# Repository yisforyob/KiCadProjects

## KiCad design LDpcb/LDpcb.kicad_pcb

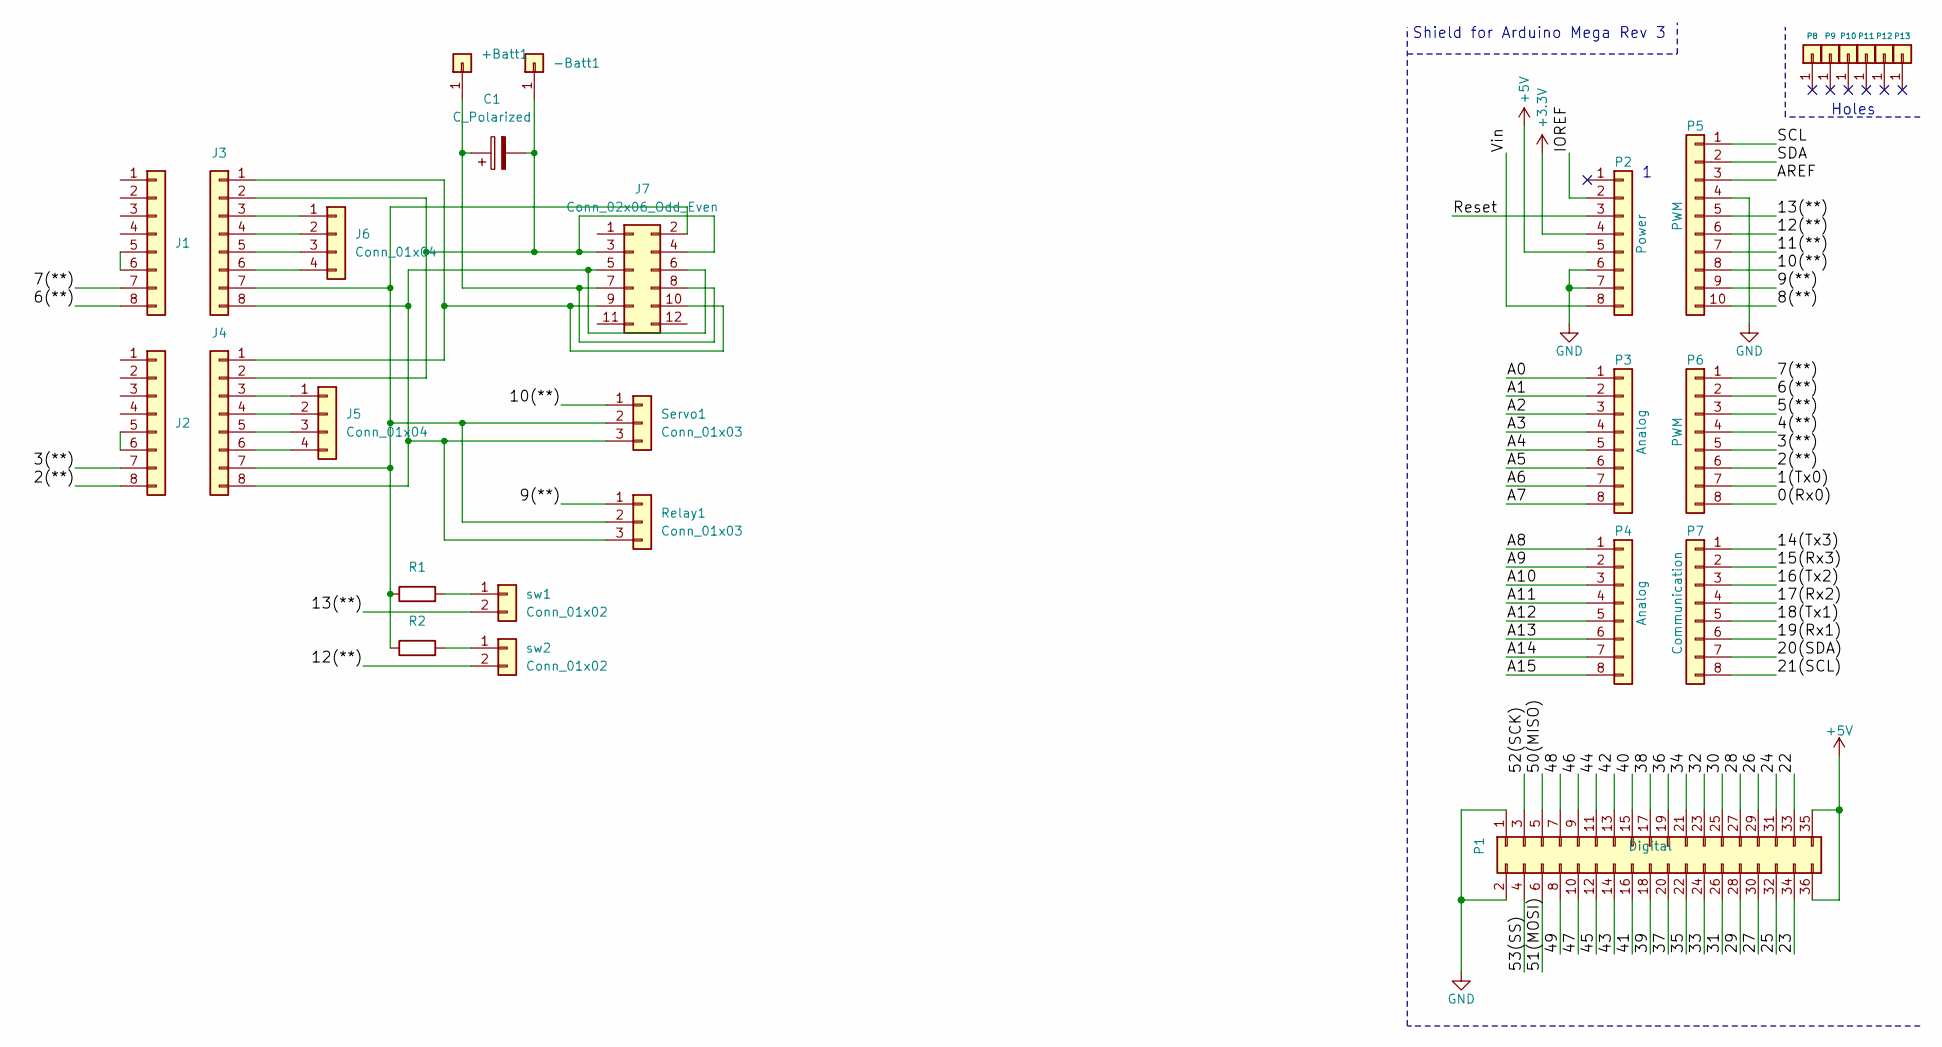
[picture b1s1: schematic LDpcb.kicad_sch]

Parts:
+Batt1: Conn_01x01; TestPoint_THTPad_D4.0mm_Drill2.0mm
-Batt1: Conn_01x01; TestPoint_THTPad_D4.0mm_Drill2.0mm
C1: C_Polarized; CP_Elec_8x6.2
J1, J2, J3, J4: Conn_01x08; PinSocket_1x08_P2.54mm_Vertical
J5, J6: Conn_01x04; PinHeader_1x04_P2.54mm_Vertical
J7: Conn_02x06_Odd_Even; PinSocket_2x06_P2.54mm_Vertical
P1: Digital; Socket_Strip_Arduino_2x18
P2: Power; Socket_Strip_Arduino_1x08
P3, P4: Analog; Socket_Strip_Arduino_1x08
P5: PWM; Socket_Strip_Arduino_1x10
P6: PWM; Socket_Strip_Arduino_1x08
P7: Communication; Socket_Strip_Arduino_1x08
P8, P9, P10, P11, P12, P13: CONN_01X01; Arduino_1pin
R1, R2: R; R_0805_2012Metric_Pad1.20x1.40mm_HandSolder
Relay1: Conn_01x03; PinSocket_1x03_P2.54mm_Vertical
Servo1: Conn_01x03; PinHeader_1x03_P2.54mm_Vertical
sw1, sw2: Conn_01x02; PinSocket_1x02_P2.54mm_Vertical

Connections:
+3V3: P2.4
+5V: P1.35, P1.36, P2.5
/0(Rx0): P6.8
/1(Tx0): P6.7
/2(**): J2.8, P6.6
/3(**): J2.7, P6.5
/4(**): P6.4
/5(**): P6.3
/6(**): J1.8, P6.2
/7(**): J1.7, P6.1
/8(**): P5.10
/9(**): P5.9, Relay1.1
/10(**): P5.8, Servo1.1
/11(**): P5.7
/12(**): P5.6, sw2.2
/13(**): P5.5, sw1.2
/14(Tx3): P7.1
/15(Rx3): P7.2
/16(Tx2): P7.3
/17(Rx2): P7.4
/18(Tx1): P7.5
/19(Rx1): P7.6
/20(SDA): P7.7
/21(SCL): P7.8
/22: P1.33
/23: P1.34
/24: P1.31
/25: P1.32
/26: P1.29
/27: P1.30
/28: P1.27
/29: P1.28
/30: P1.25
/31: P1.26
/32: P1.23
/33: P1.24
/34: P1.21
/35: P1.22
/36: P1.19
/37: P1.20
/38: P1.17
/39: P1.18
/40: P1.15
/41: P1.16
/42: P1.13
/43: P1.14
/44: P1.11
/45: P1.12
/46: P1.9
/47: P1.10
/48: P1.7
/49: P1.8
/50(MISO): P1.5
/51(MOSI): P1.6
/52(SCK): P1.3
/53(SS): P1.4
/A0: P3.1
/A1: P3.2
/A2: P3.3
/A3: P3.4
/A4: P3.5
/A5: P3.6
/A6: P3.7
/A7: P3.8
/A8: P4.1
/A9: P4.2
/A10: P4.3
/A11: P4.4
/A12: P4.5
/A13: P4.6
/A14: P4.7
/A15: P4.8
/AREF: P5.3
/IOREF: P2.2
/Reset: P2.3
/SCL: P5.1
/SDA: P5.2
/Vin: P2.8
GND: P1.1, P1.2, P2.6, P2.7, P5.4
unnamed: +Batt1.1, C1.1, J7.7, J7.8
unnamed: -Batt1.1, C1.2, J3.2, J4.2, J7.3, J7.4
unnamed: J1.5, J1.6
unnamed: J2.5, J2.6
unnamed: J3.3, J6.1
unnamed: J3.4, J6.2
unnamed: J3.5, J6.3
unnamed: J3.6, J6.4
unnamed: J4.3, J5.1
unnamed: J4.4, J5.2
unnamed: J4.5, J5.3
unnamed: J4.6, J5.4
unnamed: J3.1, J4.1, J7.9, J7.10
unnamed: J3.7, J4.7, J7.2, R1.1, R2.1, Relay1.2, Servo1.2
unnamed: J3.8, J4.8, J7.5, J7.6, Relay1.3, Servo1.3
unnamed: R1.2, sw1.1
unnamed: R2.2, sw2.1

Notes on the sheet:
Holes
Shield for Arduino Mega Rev 3

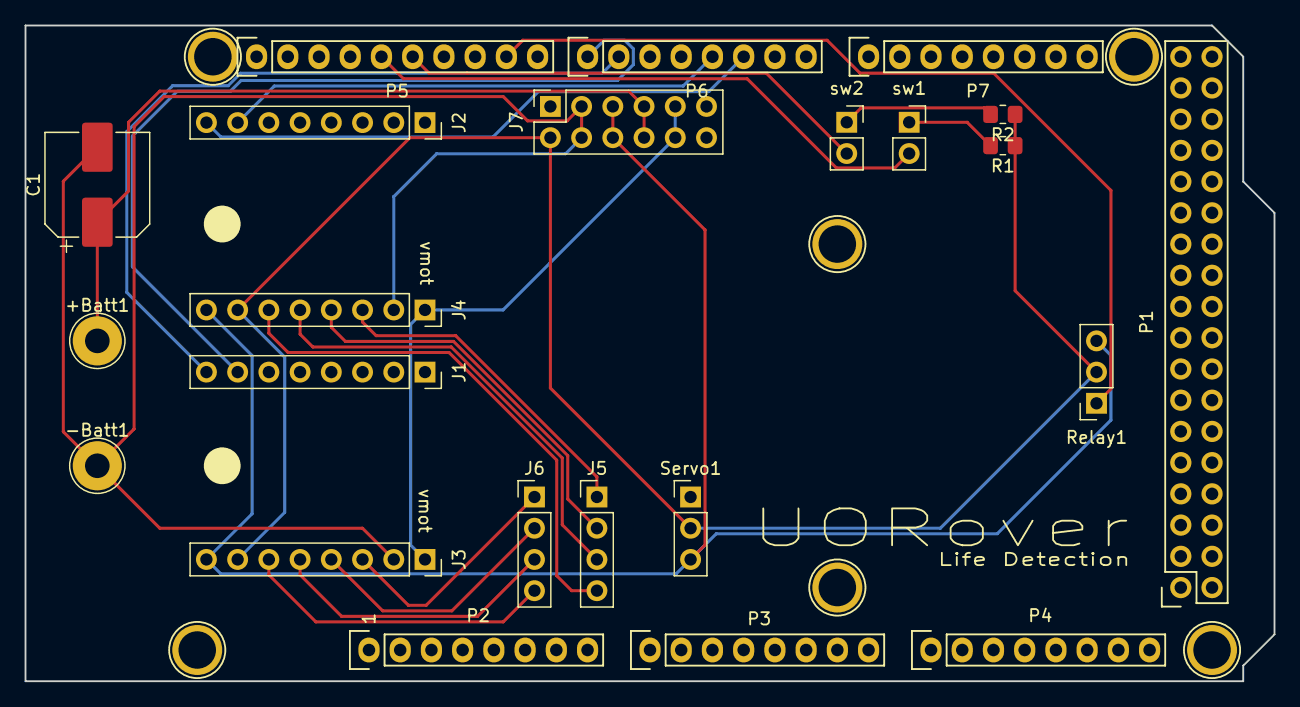
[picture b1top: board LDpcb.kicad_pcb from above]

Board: 2 copper layers, 101.6 x 53.3 mm, 29 parts (0 on the bottom side), 27 nets.

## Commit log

2023-01-16 trying not to lose my work
2023-01-16 merging everything in git
2023-01-19 new stuff from Maxime
